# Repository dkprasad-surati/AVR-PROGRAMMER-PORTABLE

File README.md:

# AVR-PROGRAMMER-PORTABLE
AVR PROGRAMMER PORTABLE UPROG PROGRAMMER
EAGLE PREMIUM VERSION DOWNLOAD :- https://drive.google.com/file/d/1bLyC4Oc8cWAWXQTi0z2VfvoDmjpry0De/view?usp=sharing

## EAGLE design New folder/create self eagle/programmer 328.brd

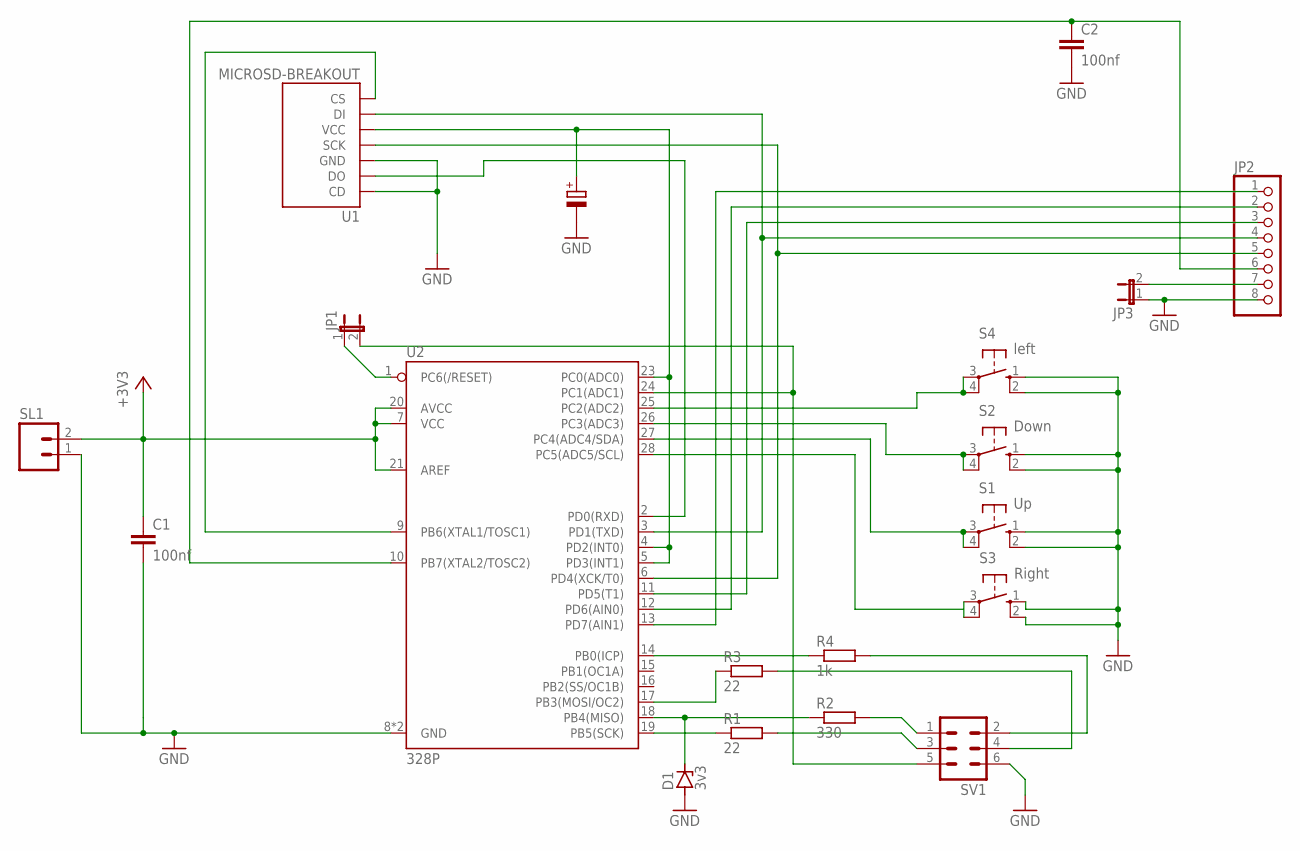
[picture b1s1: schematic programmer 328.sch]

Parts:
C1, C2: 100nf; C2.5-2
D1: 3v3; DO41Z10
JP1, JP3: JP1E; JP1
JP2: PINHD-1X8; 1X08
R1, R3: 22; 0207/12
R2: 330; 0207/12
R4: 1k; 0207/12
S1: Up; B3F-10XX
S2: Down; B3F-10XX
S3: Right; B3F-10XX
S4: left; B3F-10XX
SL1: M02; 02P
SV1: MA03-2
U1: MICROSD-BREAKOUT
U2: 328P; DIP28

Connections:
+3V3: C1.1, SL1.2, U2.7 (VCC), U2.20 (AVCC), U2.21 (AREF)
+5: R4.2, SV1.2
GND: C1.2, C2.2, D1.A, JP2.8, JP3.1, S1.1 (S), S1.2 (S1), S2.1 (S), S2.2 (S1), S3.1 (S), S3.2 (S1), S4.1 (S), S4.2 (S1), SL1.1, SV1.6, U1.CD, U1.GND, U2.8 (GND), U2.22 (GND)
unnamed: D1.C, R2.1, U2.18 (PB4(MISO))
unnamed: R1.1, U2.19 (PB5(SCK))
unnamed: R1.2, SV1.3
unnamed: R2.2, SV1.1
unnamed: JP1.1, U2.1 (PC6(/RESET))
unnamed: JP1.2, SV1.5, U2.24 (PC1(ADC1))
unnamed: R3.1, U2.17 (PB3(MOSI/OC2))
unnamed: R4.1, U2.14 (PB0(ICP))
unnamed: R3.2, SV1.4
unnamed: U1.VCC, U2.4 (PD2(INT0)), U2.5 (PD3(INT1)), U2.23 (PC0(ADC0))
unnamed: S4.3, S4.4 (P1), U2.25 (PC2(ADC2))
unnamed: S2.3, S2.4 (P1), U2.26 (PC3(ADC3))
unnamed: S1.3, S1.4 (P1), U2.27 (PC4(ADC4/SDA))
unnamed: S3.3, S3.4 (P1)
unnamed: C2.1, JP2.6, U2.10 (PB7(XTAL2/TOSC2))
unnamed: JP2.7, JP3.2
unnamed: U1.DO, U2.2 (PD0(RXD))
unnamed: JP2.5, U1.SCK, U2.6 (PD4(XCK/T0))
unnamed: JP2.4, U1.DI, U2.3 (PD1(TXD))
unnamed: JP2.3, U2.11 (PD5(T1))
unnamed: JP2.2, U2.12 (PD6(AIN0))
unnamed: JP2.1, U2.13 (PD7(AIN1))
unnamed: U1.CS, U2.9 (PB6(XTAL1/TOSC1))

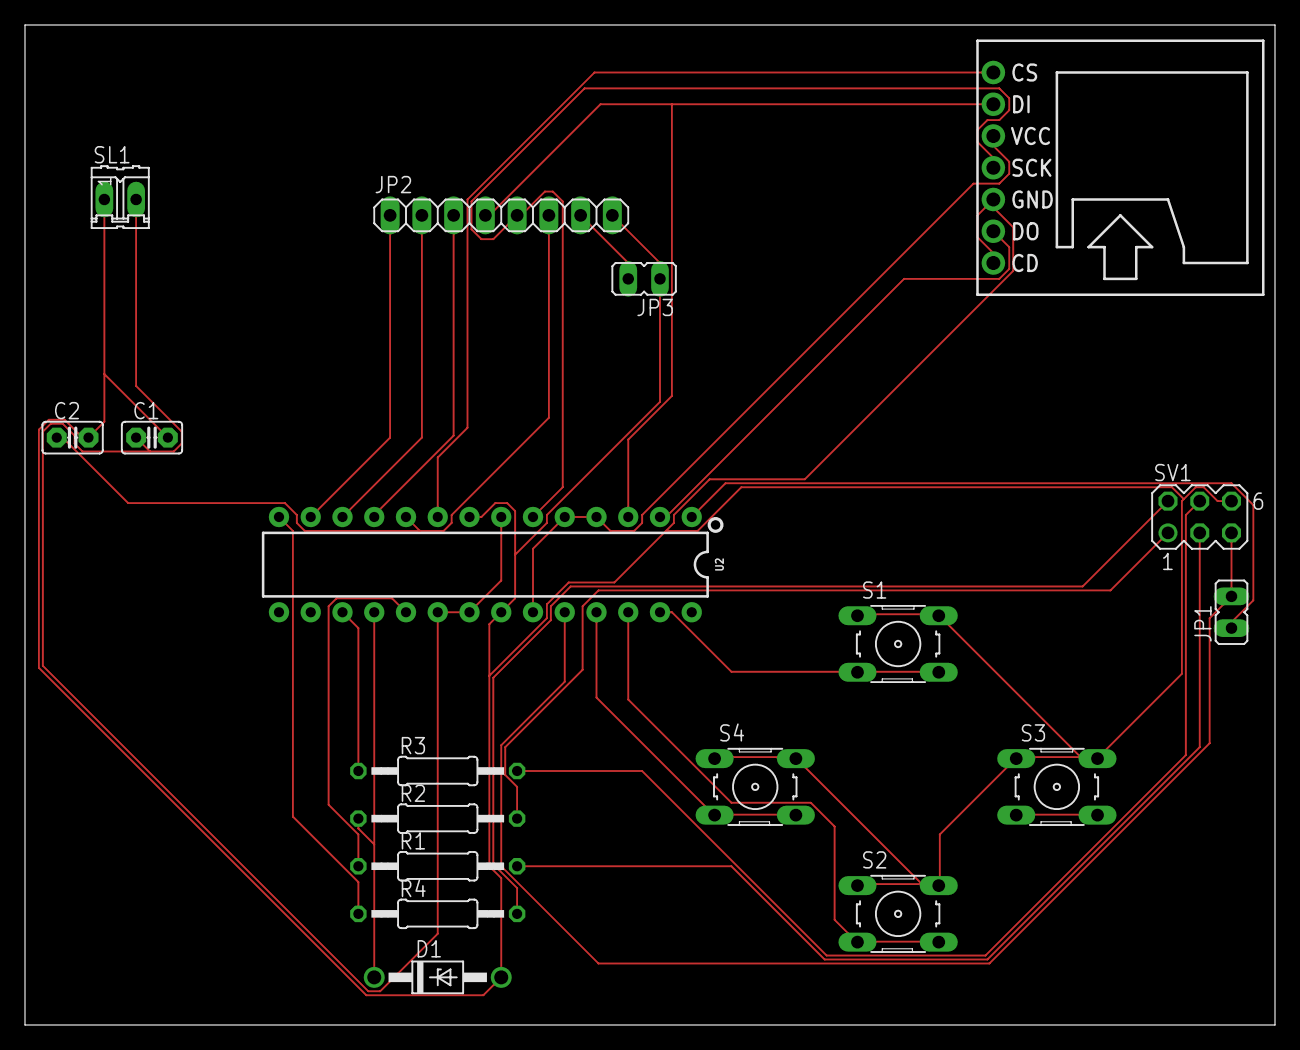
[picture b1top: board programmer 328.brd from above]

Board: 2 copper layers, 100.0 x 80.0 mm, 18 parts (0 on the bottom side), 26 nets.

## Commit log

2023-10-29 FILES

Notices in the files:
parts and their libraries:
SparkFun-Boards: Licensing: Creative Commons ShareAlike 4.0 International - https://creativecommons.org/licenses/by-sa/4.0
